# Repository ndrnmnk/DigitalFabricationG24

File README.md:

# DigitalFabricationG24

This is a repository of the project students of group 24 made during `Digital Fabrication` course in University of Oulu in 2026.

### X3mist
X3mist is a pager based on a Raspberry pi Pico. It uses RFM95w and WiFi radio module for message exchange.  
The messages are encrypted using AES-256-CBC, and the keys are exchanged through IR LED and receiver.

Other features include a 12 button keyboard and a buzzer.

### Implemented:
- AES-256-CBC message encryption
- WiFi message exchange
- IR data exchange (not used for key exchange yet)
- T9-like keyboard layout

### Not implemented:
- Key exchange
- Radio messaging
- Battery
- Mesh mode

This project may or may not be maintained further. If it is, the link will be changed.

## Footage
### Usage example:
</img>
### Assembled device:
</img>
</img>
### Pre-production PCB renders:
</img>
</img>
### Schematic:
</img>

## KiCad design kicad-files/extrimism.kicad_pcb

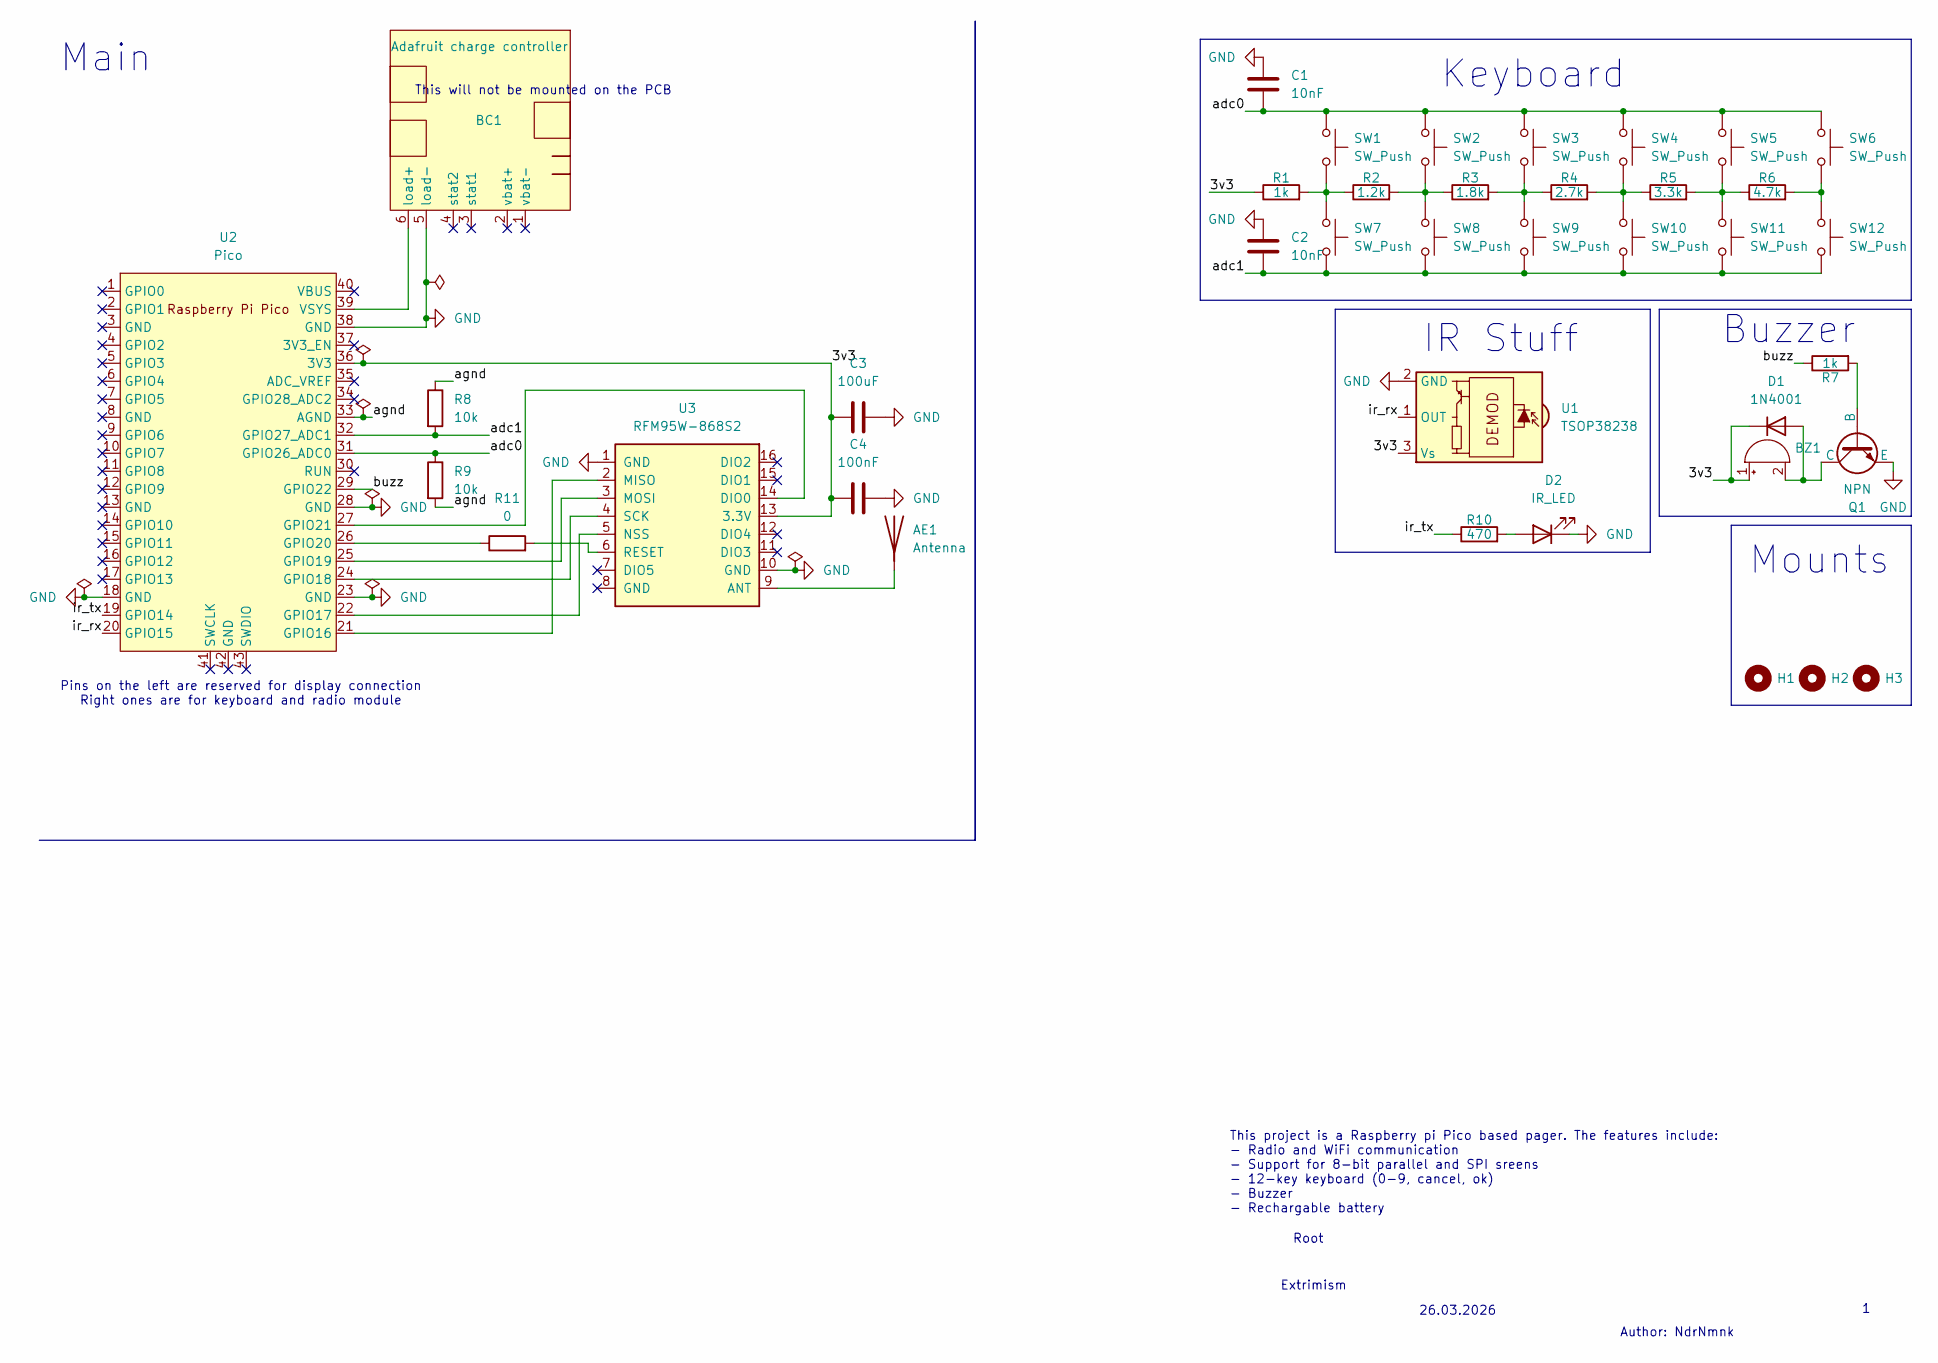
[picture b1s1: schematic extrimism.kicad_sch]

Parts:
AE1: Antenna; SolderWire-0.75sqmm_1x01_D1.25mm_OD2.3mm
BC1: Adafruit charge controller; extrimism_lib
BZ1: Buzzer; Buzzer_12x9.5RM7.6
C1, C2: 10nF; C_Disc_D5.0mm_W2.5mm_P5.00mm
C3: 100uF; C_Disc_D5.0mm_W2.5mm_P5.00mm
C4: 100nF; C_Disc_D5.0mm_W2.5mm_P5.00mm
D1: 1N4001; D_DO-41_SOD81_P10.16mm_Horizontal
D2: IR_LED; LED_D3.0mm
H1, H2, H3: MountingHole; MountingHole_2.1mm
Q1: NPN; TO-92_Inline
R1, R7: 1k; R_Axial_DIN0207_L6.3mm_D2.5mm_P7.62mm_Horizontal
R2: 1.2k; R_Axial_DIN0207_L6.3mm_D2.5mm_P7.62mm_Horizontal
R3: 1.8k; R_Axial_DIN0207_L6.3mm_D2.5mm_P7.62mm_Horizontal
R4: 2.7k; R_Axial_DIN0207_L6.3mm_D2.5mm_P7.62mm_Horizontal
R5: 3.3k; R_Axial_DIN0207_L6.3mm_D2.5mm_P7.62mm_Horizontal
R6: 4.7k; R_Axial_DIN0207_L6.3mm_D2.5mm_P7.62mm_Horizontal
R8, R9: 10k; R_Axial_DIN0207_L6.3mm_D2.5mm_P7.62mm_Horizontal
R10: 470; R_Axial_DIN0207_L6.3mm_D2.5mm_P7.62mm_Horizontal
R11: 0; R_Axial_DIN0207_L6.3mm_D2.5mm_P7.62mm_Horizontal
SW1, SW2, SW3, SW4, SW5, SW6, SW7, SW8, SW9, SW10, SW11, SW12: SW_Push; SW_PUSH_6mm
U1: TSOP38238; Vishay_MINICAST-3Pin
U2: Pico; RPi_Pico_SMD_TH
U3: RFM95W-868S2; HOPERF_RFM9XW_SMD

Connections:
/3v3: BZ1.1 (+), C3.1, C4.1, D1.1 (K), R1.1, U1.3 (Vs), U2.36 (3V3), U3.13 (3.3V)
/adc0: C1.1, R9.1, SW1.1, SW2.1, SW3.1, SW4.1, SW5.1, SW6.1, U2.31 (GPIO26_ADC0)
/adc1: C2.1, R8.2, SW7.2, SW8.2, SW9.2, SW10.2, SW11.2, SW12.2, U2.32 (GPIO27_ADC1)
/agnd: R8.1, R9.2, U2.33 (AGND)
/buzz: R7.1, U2.29 (GPIO22)
/ir_rx: U1.1 (OUT), U2.20 (GPIO15)
/ir_tx: R10.1, U2.19 (GPIO14)
GND: BC1.5 (load-), C1.2, C2.2, C3.2, C4.2, D2.1 (K), Q1.3 (E), U1.2 (GND), U2.18 (GND), U2.23 (GND), U2.28 (GND), U2.38 (GND), U3.1 (GND), U3.10 (GND)
unnamed: AE1.1 (A), U3.9 (ANT)
unnamed: BC1.6 (load+), U2.39 (VSYS)
unnamed: BZ1.2 (-), D1.2 (A), Q1.1 (C)
unnamed: D2.2 (A), R10.2
unnamed: Q1.2 (B), R7.2
unnamed: R1.2, R2.1, SW1.2, SW7.1
unnamed: R2.2, R3.1, SW2.2, SW8.1
unnamed: R3.2, R4.1, SW3.2, SW9.1
unnamed: R4.2, R5.1, SW4.2, SW10.1
unnamed: R5.2, R6.1, SW5.2, SW11.1
unnamed: R6.2, SW6.2, SW12.1
unnamed: U2.21 (GPIO16), U3.2 (MISO)
unnamed: U2.22 (GPIO17), U3.5 (NSS)
unnamed: U2.24 (GPIO18), U3.4 (SCK)
unnamed: U2.25 (GPIO19), U3.3 (MOSI)
unnamed: R11.1, U2.26 (GPIO20)
unnamed: U2.27 (GPIO21), U3.14 (DIO0)
unnamed: R11.2, U3.6 (RESET)

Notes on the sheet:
Main
IR Stuff
Mounts
This project is a Raspberry pi Pico based pager. The features include: - Radio and WiFi communication - Support for 8-bit parallel and SPI sreens - 12-key keyboard (0-9, cancel, ok) - Buzzer - Rechargable battery
Author: NdrNmnk
Root
Buzzer
Keyboard
Pins on the left are reserved for display connection Right ones are for keyboard and radio module
26.03.2026
Extrimism
This will not be mounted on the PCB

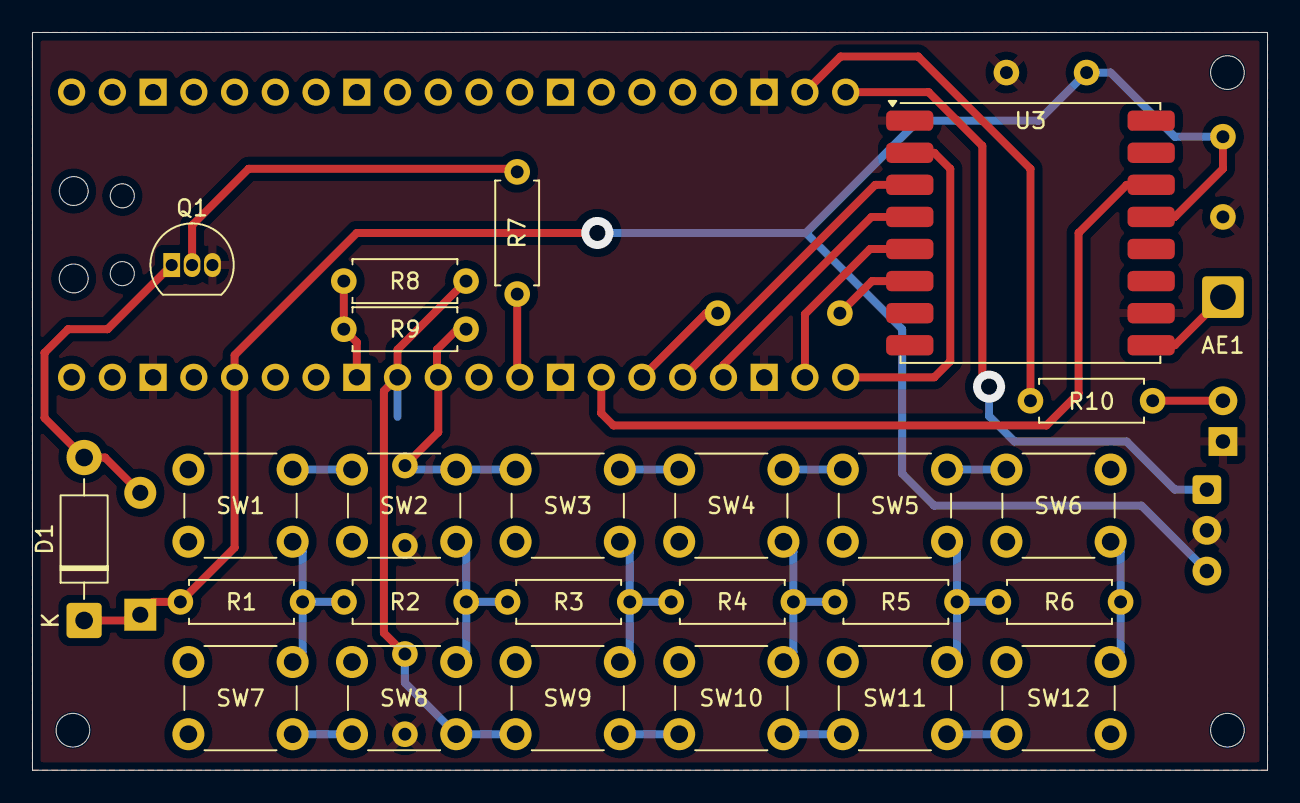
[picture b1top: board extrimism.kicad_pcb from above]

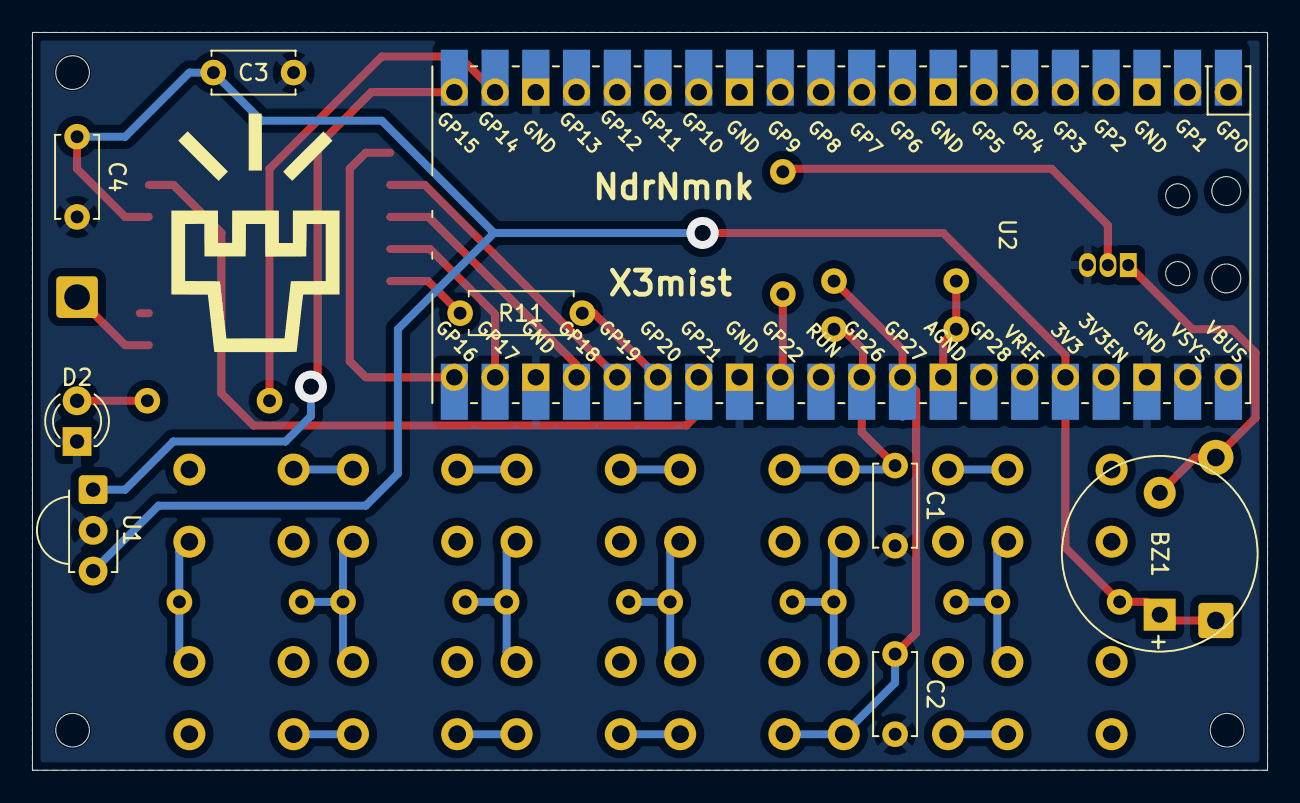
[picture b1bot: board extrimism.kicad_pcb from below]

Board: 2 copper layers, 77.0 x 46.0 mm, 38 parts (9 on the bottom side), 25 nets.

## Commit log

2026-03-26 added PCB
2026-04-30 Add files via upload
    PoDF_A is for the E-INK display and PoDF is for the LCD
2026-05-02 updated PCB design
2026-05-04 added images
2026-05-04 Acrylic backplate for the case
2026-05-04 added usage gif
2026-05-04 Update README with features and usage examples
    Added sections for implemented and not implemented features, along with usage examples and images of the assembled device and PCB renders.
